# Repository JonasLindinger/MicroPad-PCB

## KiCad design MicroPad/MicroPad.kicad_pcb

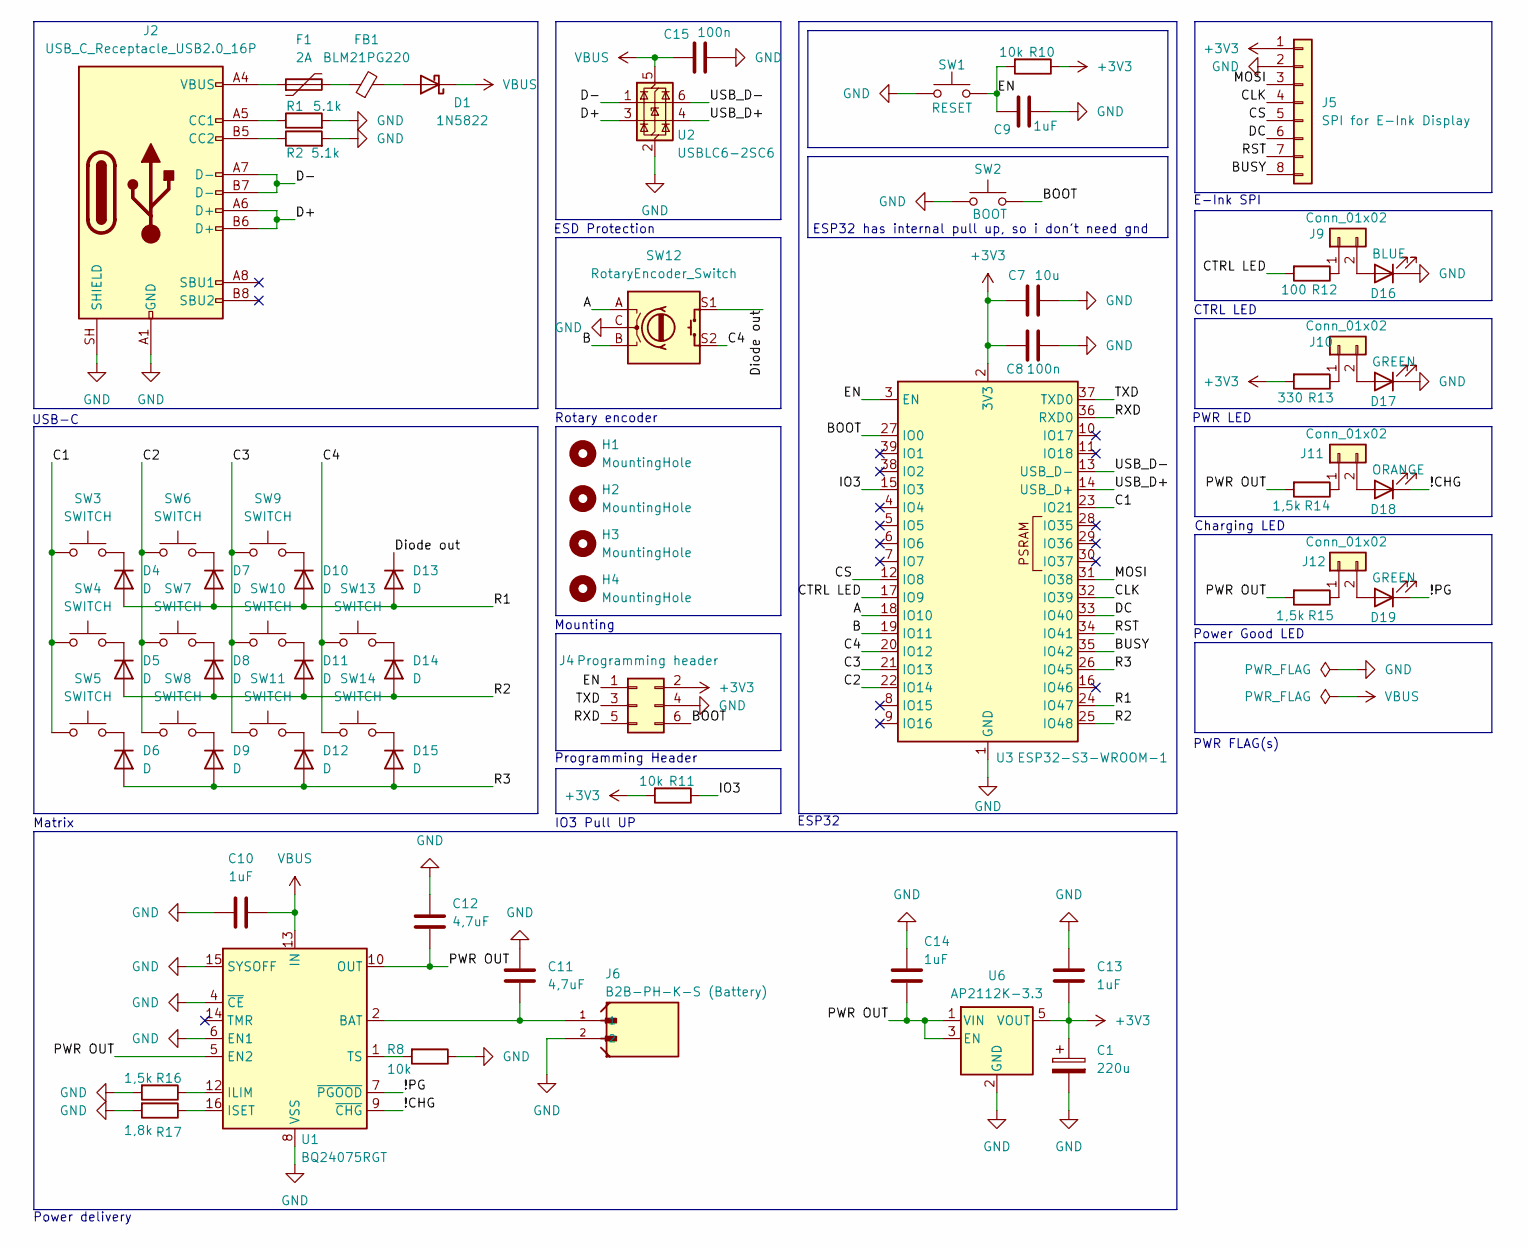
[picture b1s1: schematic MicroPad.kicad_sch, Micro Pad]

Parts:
C1: 220u; CP_Elec_6.3x7.7
C7: 10u; C_0805_2012Metric_Pad1.18x1.45mm_HandSolder
C8, C15: 100n; C_0805_2012Metric_Pad1.18x1.45mm_HandSolder
C9, C10, C13, C14: 1uF; C_0805_2012Metric_Pad1.18x1.45mm_HandSolder
C11, C12: 4,7uF; C_0805_2012Metric_Pad1.18x1.45mm_HandSolder
D1: 1N5822; D_DO-201AD_P15.24mm_Horizontal
D4, D5, D6, D7, D8, D9, D10, D11, D12, D13, D14, D15: D; D_SMA
D16: BLUE; LED_D3.0mm
D17, D19: GREEN; LED_D3.0mm
D18: ORANGE; LED_D3.0mm
F1: 2A; Fuse_0805_2012Metric_Pad1.15x1.40mm_HandSolder
FB1: BLM21PG220; L_0805_2012Metric_Pad1.05x1.20mm_HandSolder
H1, H2, H3, H4: MountingHole; MountingHole_3.2mm_M3_DIN965
J2: USB_C_Receptacle_USB2.0_16P; USB_C_Receptacle_GCT_USB4085
J4: Programming header; PinHeader_2x03_P2.54mm_Vertical
J5: SPI for E-Ink Display; PinHeader_1x08_P2.54mm_Vertical
J6: B2B-PH-K-S (Battery); JST_B2B-PH-K-S
J9, J10, J11, J12: Conn_01x02; SolderJumper-2_P1.3mm_Open_TrianglePad1.0x1.5mm
R1, R2: 5.1k; R_0805_2012Metric_Pad1.20x1.40mm_HandSolder
R8, R10, R11: 10k; R_0805_2012Metric_Pad1.20x1.40mm_HandSolder
R12: 100; R_0805_2012Metric_Pad1.20x1.40mm_HandSolder
R13: 330; R_0805_2012Metric_Pad1.20x1.40mm_HandSolder
R14, R15, R16: 1,5k; R_0805_2012Metric_Pad1.20x1.40mm_HandSolder
R17: 1,8k; R_0805_2012Metric_Pad1.20x1.40mm_HandSolder
SW1: RESET; SW_PUSH_6mm
SW2: BOOT; SW_PUSH_6mm
SW3, SW4, SW5, SW6, SW7, SW8, SW9, SW10, SW11, SW13, SW14: SWITCH; SW_Cherry_MX_1.00u_PCB
SW12: RotaryEncoder_Switch; RotaryEncoder_Alps_EC11E-Switch_Vertical_H20mm
U1: BQ24075RGT; VQFN-16-1EP_3x3mm_P0.5mm_EP1.6x1.6mm
U2: USBLC6-2SC6; SOT-23-6
U3: ESP32-S3-WROOM-1
U6: AP2112K-3.3; SOT-23-5

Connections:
+3V3: C1.1, C7.1, C8.1, C13.2, J4.2, J5.1, R10.1, R11.2, R13.2, U3.2 (3V3), U6.5 (VOUT)
/!CHG: D18.1 (K), U1.9 (~CHG)
/!PG: D19.1 (K), U1.7 (~PGOOD)
/A: SW12.A, U3.18 (IO10)
/B: SW12.B, U3.19 (IO11)
/BOOT: J4.6, SW2.2, U3.27 (IO0)
/BUSY: J5.8, U3.35 (IO42)
/C1: SW3.1, SW4.1, SW5.1, U3.23 (IO21)
/C2: SW6.1, SW7.1, SW8.1, U3.22 (IO14)
/C3: SW9.1, SW10.1, SW11.1, U3.21 (IO13)
/C4: SW12.S2, SW13.1, SW14.1, U3.20 (IO12)
/CLK: J5.4, U3.32 (IO39)
/CS: J5.5, U3.12 (IO8)
/CTRL LED: R12.2, U3.17 (IO9)
/D+: J2.A6 (D+), J2.B6 (D+), U2.3 (I/O2)
/D-: J2.A7 (D-), J2.B7 (D-), U2.1 (I/O1)
/DC: J5.6, U3.33 (IO40)
/Diode out: D13.1 (K), SW12.S1
/EN: C9.1, J4.1, R10.2, SW1.2, U3.3 (EN)
/IO3: R11.1, U3.15 (IO3)
/MOSI: J5.3, U3.31 (IO38)
/PWR OUT: C12.2, C14.2, R14.2, R15.2, U1.5 (EN2), U1.10 (OUT), U1.11 (OUT), U6.1 (VIN), U6.3 (EN)
/R1: D4.2 (A), D7.2 (A), D10.2 (A), D13.2 (A), U3.24 (IO47)
/R2: D5.2 (A), D8.2 (A), D11.2 (A), D14.2 (A), U3.25 (IO48)
/R3: D6.2 (A), D9.2 (A), D12.2 (A), D15.2 (A), U3.26 (IO45)
/RST: J5.7, U3.34 (IO41)
/RXD: J4.5, U3.36 (RXD0)
/TXD: J4.3, U3.37 (TXD0)
/USB_D+: U2.4 (I/O2), U3.14 (USB_D+)
/USB_D-: U2.6 (I/O1), U3.13 (USB_D-)
GND: C1.2, C7.2, C8.2, C9.2, C10.2, C11.1, C12.1, C13.1, C14.1, C15.2, D16.1 (K), D17.1 (K), J2.A1 (GND), J2.A12 (GND), J2.B1 (GND), J2.B12 (GND), J2.SH (SHIELD), J4.4, J5.2, J6.2, R1.2, R2.2, R8.1, R16.2, R17.2, SW1.1, SW2.1, SW12.C, U1.4 (~CE), U1.6 (EN1), U1.8 (VSS), U1.15 (SYSOFF), U1.17 (VSS), U2.2 (GND), U3.1 (GND), U3.40 (GND), U3.41 (GND), U6.2 (GND)
unnamed: C11.2, J6.1, U1.2 (BAT), U1.3 (BAT)
unnamed: D1.2 (A), FB1.2
unnamed: D4.1 (K), SW3.2
unnamed: D5.1 (K), SW4.2
unnamed: D6.1 (K), SW5.2
unnamed: D7.1 (K), SW6.2
unnamed: D8.1 (K), SW7.2
unnamed: D9.1 (K), SW8.2
unnamed: D10.1 (K), SW9.2
unnamed: D11.1 (K), SW10.2
unnamed: D12.1 (K), SW11.2
unnamed: D14.1 (K), SW13.2
unnamed: D15.1 (K), SW14.2
unnamed: D16.2 (A), J9.2
unnamed: D17.2 (A), J10.2
unnamed: D18.2 (A), J11.2
unnamed: D19.2 (A), J12.2
unnamed: F1.1, J2.A4 (VBUS), J2.A9 (VBUS), J2.B4 (VBUS), J2.B9 (VBUS)
unnamed: F1.2, FB1.1
unnamed: J2.A5 (CC1), R1.1
unnamed: J2.B5 (CC2), R2.1
unnamed: J9.1, R12.1
unnamed: J10.1, R13.1
unnamed: J11.1, R14.1
unnamed: J12.1, R15.1
unnamed: R16.1, U1.12 (ILIM)
unnamed: R17.1, U1.16 (ISET)
unnamed: R8.2, U1.1 (TS)
VBUS: C10.1, C15.1, D1.1 (K), U1.13 (IN), U2.5 (VBUS)

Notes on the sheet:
CTRL LED
PWR FLAG(s)
PWR LED
ESP32
E-Ink SPI
IO3 Pull UP
Programming Header
Matrix
ESD Protection
Power delivery
Rotary encoder
Power Good LED
Mounting
Charging LED
ESP32 has internal pull up, so i don't need gnd
USB-C

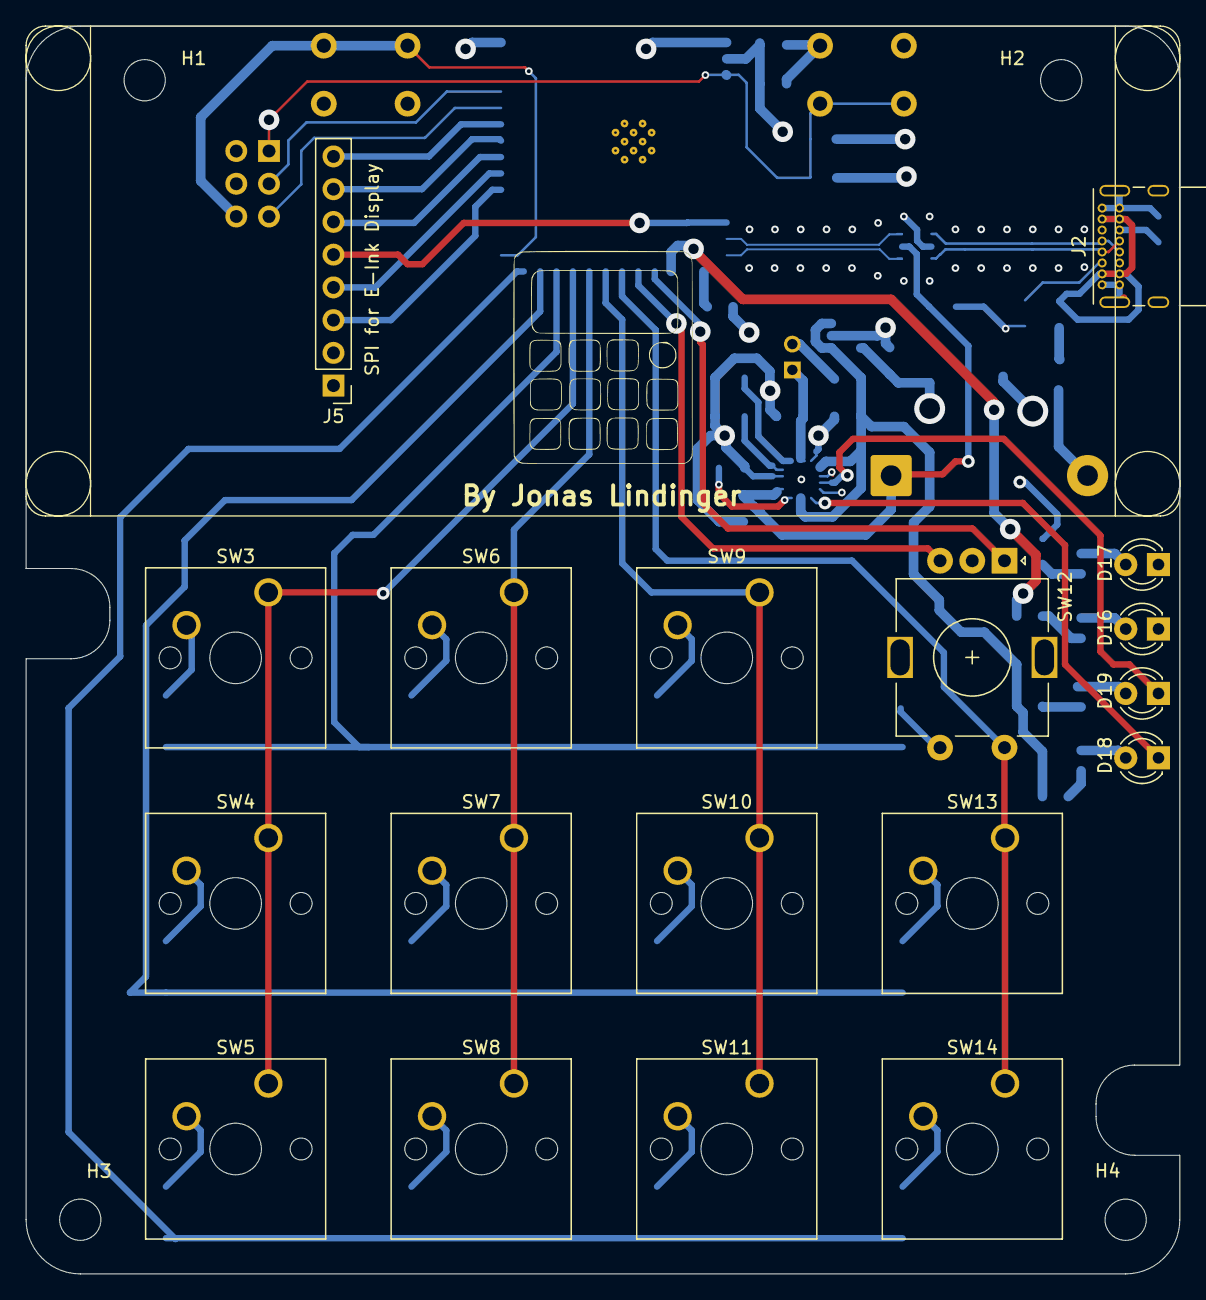
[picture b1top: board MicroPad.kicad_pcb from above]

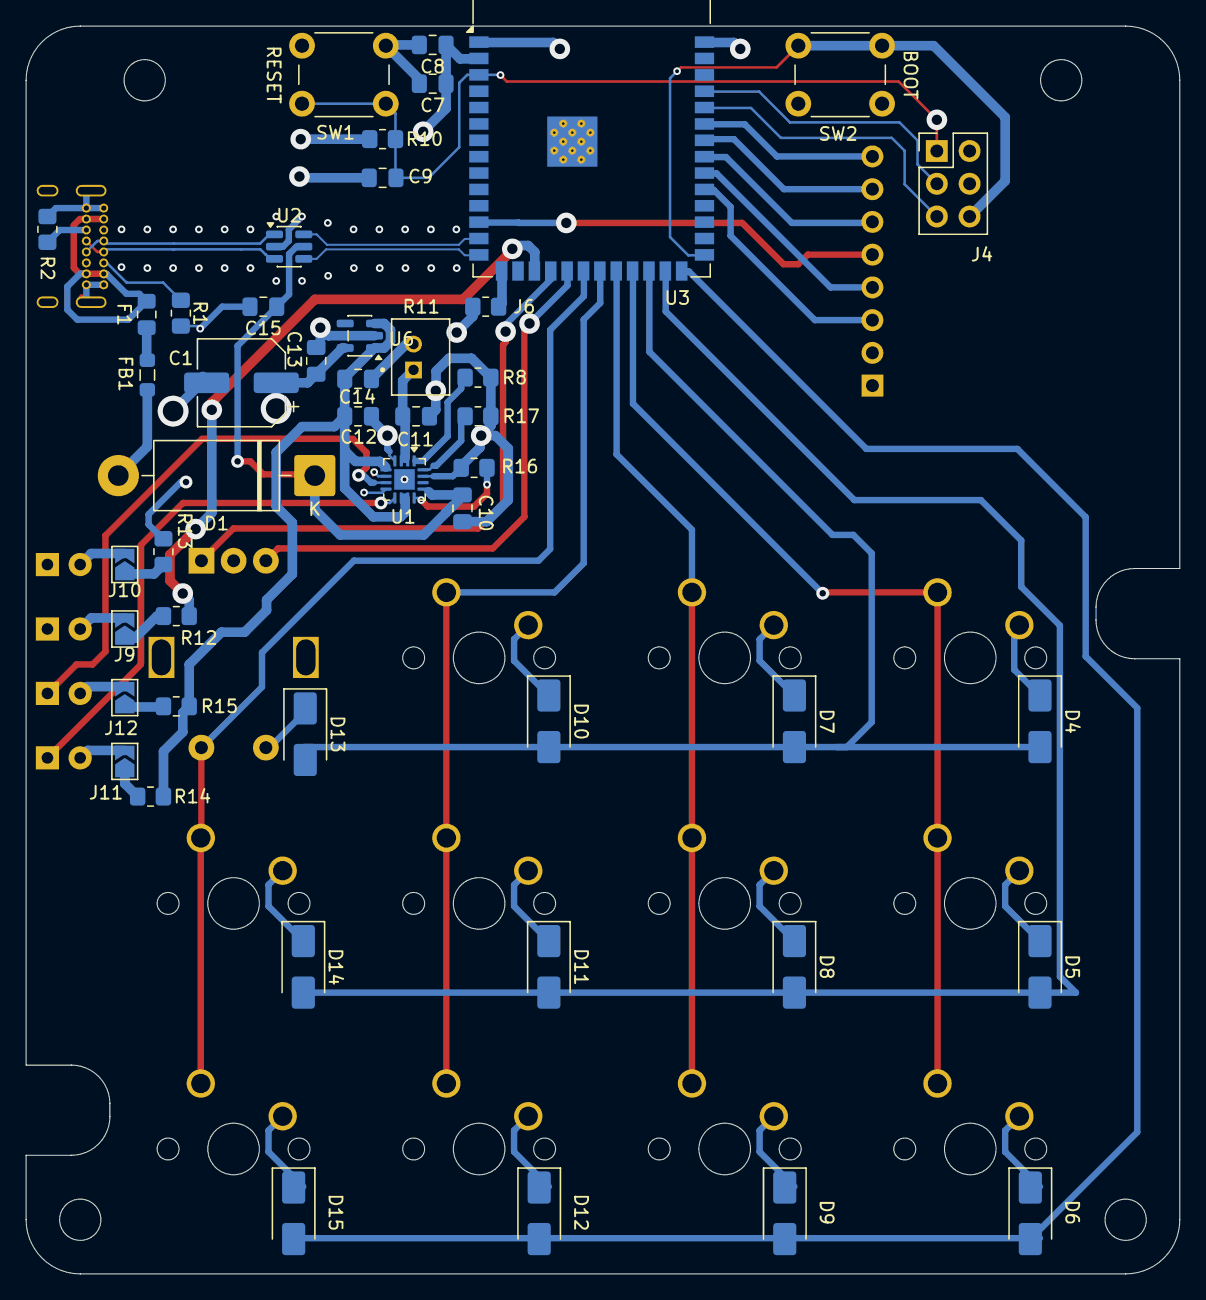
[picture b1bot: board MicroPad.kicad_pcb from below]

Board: 4 copper layers, 89.5 x 96.8 mm, 70 parts (48 on the bottom side), 60 nets.

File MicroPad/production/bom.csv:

Designator,Footprint,Quantity,Value,LCSC Part #
C1,CP_Elec_6.3x7.7,1,220u,
"C10, C13, C14, C9",0805,4,1uF,
"C11, C12",0805,2,"4,7uF",
"C15, C8",0805,2,100n,
C7,0805,1,10u,
D1,D_DO-201AD_P15.24mm_Horizontal,1,1N5822,
"D10, D11, D12, D13, D14, D15, D4, D5, D6, D7, D8, D9",D_SMA,12,D,
D16,LED_D3.0mm,1,BLUE,
"D17, D19",LED_D3.0mm,2,GREEN,
D18,LED_D3.0mm,1,ORANGE,
F1,0805,1,2A,
FB1,0805,1,BLM21PG220,
"J10, J11, J12, J9",SolderJumper-2_P1.3mm_Open_TrianglePad1.0x1.5mm,4,Conn_01x02,
J2,USB_C_Receptacle_GCT_USB4085,1,USB_C_Receptacle_USB2.0_16P,
J4,PinHeader_2x03_P2.54mm_Vertical,1,Programming header,
J5,PinHeader_1x08_P2.54mm_Vertical,1,SPI for E-Ink Display,
J6,JST_B2B-PH-K-S,1,B2B-PH-K-S (Battery),
"R1, R2",0805,2,5.1k,
"R10, R11, R8",0805,3,10k,
R12,0805,1,100,
R13,0805,1,330,
"R14, R15, R16",0805,3,"1,5k",
R17,0805,1,"1,8k",
SW1,SW_PUSH_6mm,1,RESET,
"SW10, SW11, SW13, SW14, SW3, SW4, SW5, SW6, SW7, SW8, SW9",SW_Cherry_MX_1.00u_PCB,11,SWITCH,
SW12,RotaryEncoder_Alps_EC11E-Switch_Vertical_H20mm,1,RotaryEncoder_Switch,
SW2,SW_PUSH_6mm,1,BOOT,
U1,VQFN-16-1EP_3x3mm_P0.5mm_EP1.6x1.6mm,1,BQ24075RGT,
U2,SOT-23-6,1,USBLC6-2SC6,
U3,ESP32-S3-WROOM-1,1,ESP32-S3-WROOM-1,
U6,SOT-23-5,1,AP2112K-3.3,
